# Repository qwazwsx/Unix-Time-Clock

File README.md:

# Introduction

This project is a fork of [Maniacal Labs Super 7 Seg](https://github.com/ManiacalLabs/Super7Seg). Please refer to that project's README for the full details of that project.

My fork was designed with one project in mind - creating a [Unix Time Clock](https://mylifeasa.tinkerer.us/unix-time-clock-57b17d05442e). To accomplish this, I changed the [display hardware](https://github.com/dwaq/Super7Seg/tree/master/kicad/Super7Display) from 6x dual segment displays to 5x displays (12 digits to 10 digits) and changed the [controller hardware](https://github.com/dwaq/Super7Seg/tree/master/kicad/Super7Controller) from a ATMega328p to ESP32. The [Arduino firmware](https://github.com/dwaq/Super7Seg/tree/master/Firmware-ESP32) for this project is also in this repo, along with the [3D models](https://github.com/dwaq/Super7Seg/tree/master/Mount-ESP32) for mounting the project.

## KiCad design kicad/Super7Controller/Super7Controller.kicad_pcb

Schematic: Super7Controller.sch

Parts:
P3: Conn_01x13; Socket_Strip_Straight_1x13_Pitch2.54mm
P4: Conn_01x09; Socket_Strip_Straight_1x09_Pitch2.54mm
R1, R2, R3, R5, R6, R7, R8, R10, R11, R12, R13, R14, R15, R16: 120; R_0805_HandSoldering
U1: ULN2003A; SOIC-16_3.9x9.9mm_Pitch1.27mm
U2: HiLetgo_ESP-WROOM-32_Development_Board; hiletgo_esp-wroom-32_development_board

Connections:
DCD_1: U1.6 (I6), U2.15 (P13)
DCD_2: U1.5 (I5), U2.27 (P16)
DCD_3: U1.4 (I4), U2.26 (P4)
DCD_4: U1.3 (I3), U2.25 (P0)
DCD_5: U1.2 (I2), U2.24 (P2)
DCD_6: U1.1 (I1), U2.23 (P15)
DC_1: P3.1, U1.11 (O6)
DC_2: P3.2, U1.12 (O5)
DC_3: P3.7, U1.13 (O4)
DC_4: P3.8, U1.14 (O3)
DC_5: P3.12, U1.15 (O2)
DC_6: P3.13, U1.16 (O1)
GND: U1.8 (GND), U2.14 (GND)
H_A1: P3.5, R12.2
H_A2: P3.10, R15.2
H_B1: P3.6, R13.2
H_B2: P3.11, R16.2
H_C1: P4.3, R3.2
H_C2: P4.8, R8.2
H_D1: P4.2, R2.2
H_D2: P4.6, R6.2
H_E1: P4.1, R1.2
H_E2: P4.5, R5.2
H_F1: P3.3, R10.2
H_F2: P3.9, R14.2
H_G1: P3.4, R11.2
H_G2: P4.7, R7.2
unnamed: R1.1, U2.13 (P12)
unnamed: R2.1, U2.12 (P14)
unnamed: R3.1, U2.11 (P27)
unnamed: R5.1, U2.9 (P25)
unnamed: R6.1, U2.8 (P33)
unnamed: R7.1, U2.7 (P32)
unnamed: R8.1, U2.10 (P26)
unnamed: R10.1, U2.28 (P17)
unnamed: R11.1, U2.29 (P5)
unnamed: R12.1, U2.30 (P18)
unnamed: R13.1, U2.31 (P19)
unnamed: R14.1, U2.33 (P21)
unnamed: R15.1, U2.36 (P22)
unnamed: R16.1, U2.37, U2.38 (P23)

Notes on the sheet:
Ran out of GPIO outputs to control these pins

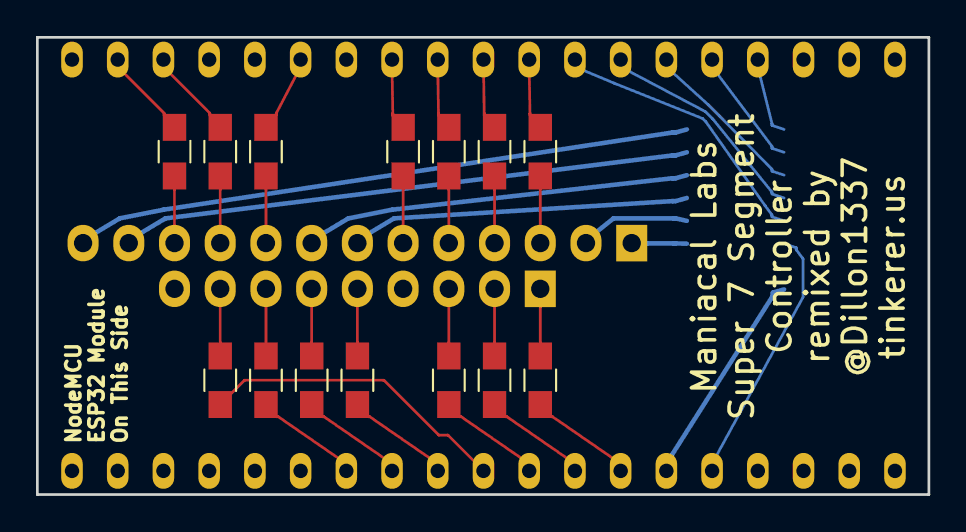
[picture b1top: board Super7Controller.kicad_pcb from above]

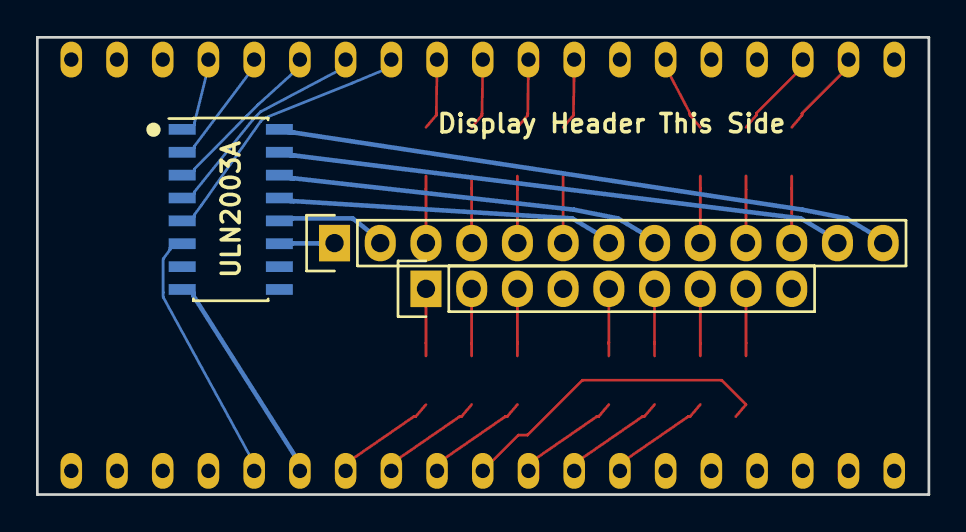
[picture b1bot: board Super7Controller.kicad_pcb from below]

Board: 2 copper layers, 49.5 x 25.4 mm, 18 parts (3 on the bottom side), 41 nets.

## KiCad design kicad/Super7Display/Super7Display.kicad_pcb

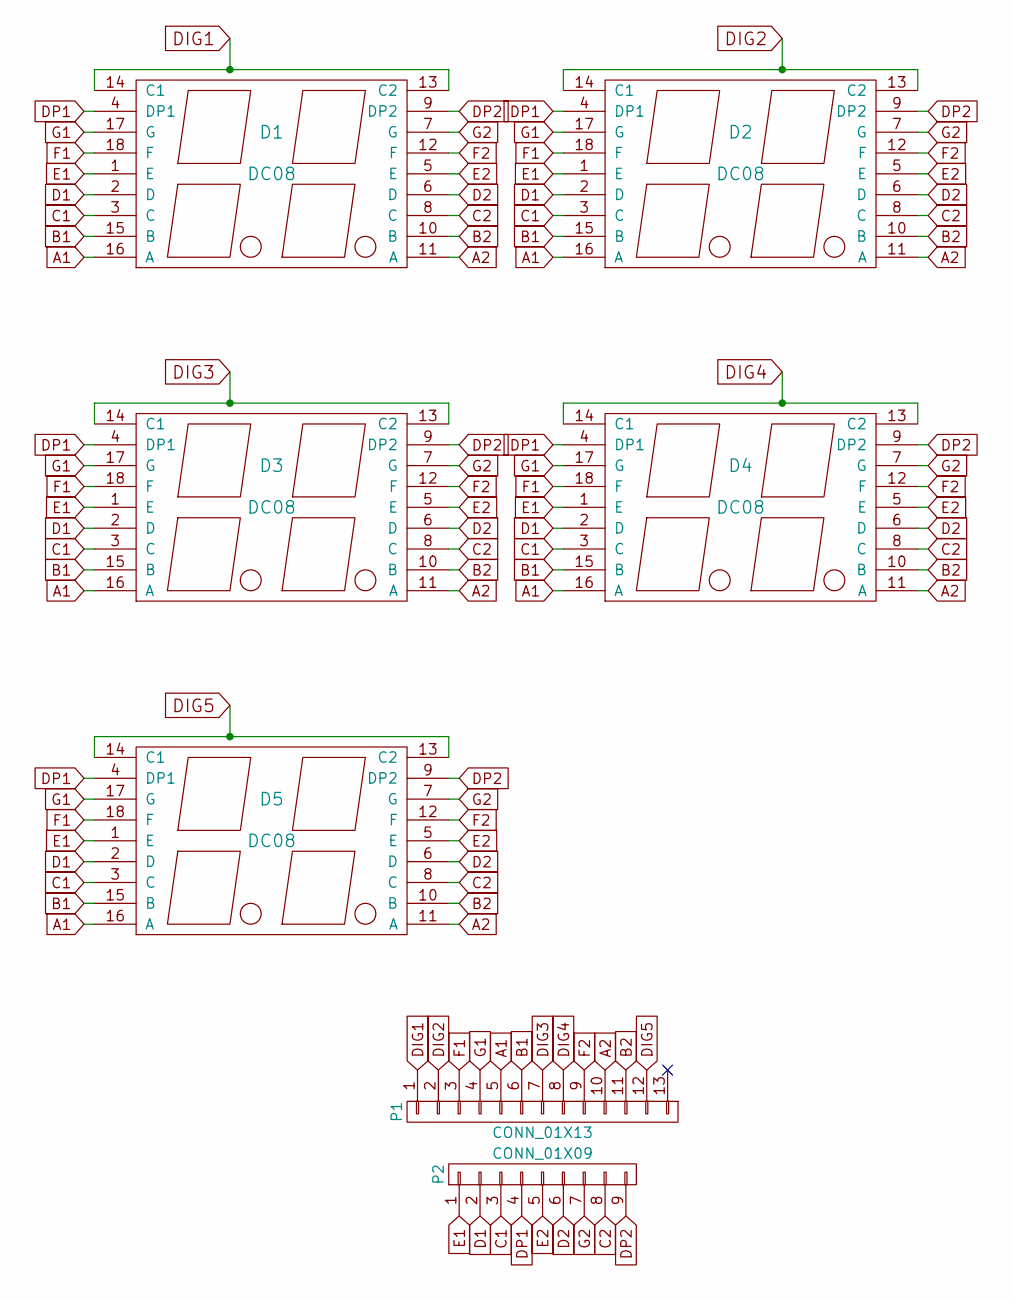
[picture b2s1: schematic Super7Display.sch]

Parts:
D1, D2, D3, D4, D5: DC08
P1: CONN_01X13; Socket_Strip_Straight_1x13
P2: CONN_01X09; Socket_Strip_Straight_1x09

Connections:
A1: D1.16 (A), D2.16 (A), D3.16 (A), D4.16 (A), D5.16 (A), P1.5
A2: D1.11 (A), D2.11 (A), D3.11 (A), D4.11 (A), D5.11 (A), P1.10
B1: D1.15 (B), D2.15 (B), D3.15 (B), D4.15 (B), D5.15 (B), P1.6
B2: D1.10 (B), D2.10 (B), D3.10 (B), D4.10 (B), D5.10 (B), P1.11
C1: D1.3 (C), D2.3 (C), D3.3 (C), D4.3 (C), D5.3 (C), P2.3
C2: D1.8 (C), D2.8 (C), D3.8 (C), D4.8 (C), D5.8 (C), P2.8
D1: D1.2 (D), D2.2 (D), D3.2 (D), D4.2 (D), D5.2 (D), P2.2
D2: D1.6 (D), D2.6 (D), D3.6 (D), D4.6 (D), D5.6 (D), P2.6
DIG1: D1.13 (C2), D1.14 (C1), P1.1
DIG2: D2.13 (C2), D2.14 (C1), P1.2
DIG3: D3.13 (C2), D3.14 (C1), P1.7
DIG4: D4.13 (C2), D4.14 (C1), P1.8
DIG5: D5.13 (C2), D5.14 (C1), P1.12
DP1: D1.4 (DP1), D2.4 (DP1), D3.4 (DP1), D4.4 (DP1), D5.4 (DP1), P2.4
DP2: D1.9 (DP2), D2.9 (DP2), D3.9 (DP2), D4.9 (DP2), D5.9 (DP2), P2.9
E1: D1.1 (E), D2.1 (E), D3.1 (E), D4.1 (E), D5.1 (E), P2.1
E2: D1.5 (E), D2.5 (E), D3.5 (E), D4.5 (E), D5.5 (E), P2.5
F1: D1.18 (F), D2.18 (F), D3.18 (F), D4.18 (F), D5.18 (F), P1.3
F2: D1.12 (F), D2.12 (F), D3.12 (F), D4.12 (F), D5.12 (F), P1.9
G1: D1.17 (G), D2.17 (G), D3.17 (G), D4.17 (G), D5.17 (G), P1.4
G2: D1.7 (G), D2.7 (G), D3.7 (G), D4.7 (G), D5.7 (G), P2.7

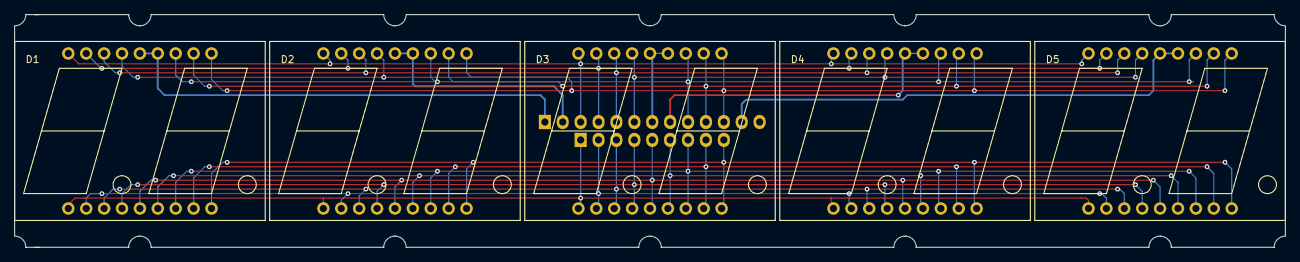
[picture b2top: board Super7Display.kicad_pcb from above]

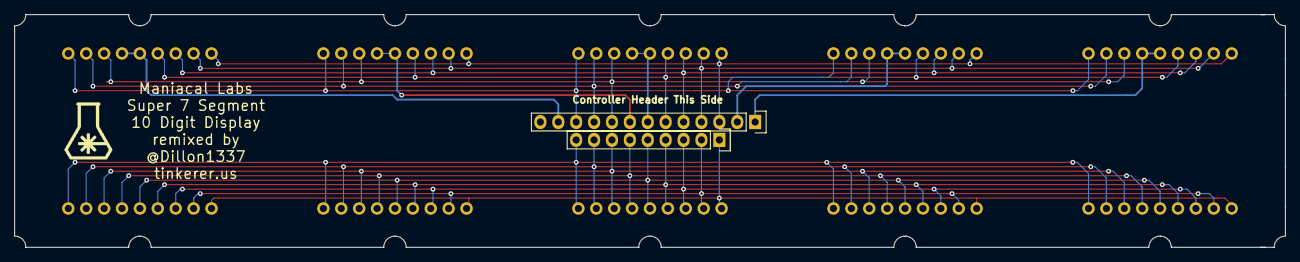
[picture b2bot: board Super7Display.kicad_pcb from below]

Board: 2 copper layers, 180.3 x 33.0 mm, 7 parts (2 on the bottom side), 21 nets.

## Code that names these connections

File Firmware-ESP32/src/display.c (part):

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
// digit is active high
// digit | ESP32 pin
#define DC_1  13
#define DC_2  16
#define DC_3  4
#define DC_4  0
#define DC_5  2
#define DC_6  15

// PWM channels cooresponding to digits
#define D_PWM_1  1
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  //pinMode(SEG_DP2, OUTPUT);

  // set up PWM on digits
  ledcAttachPin(DC_1, D_PWM_1);
  ledcSetup(D_PWM_1, PWM_FREQ, PWM_RESOLUTION);

  ledcAttachPin(DC_2, D_PWM_2);
  ledcSetup(D_PWM_2, PWM_FREQ, PWM_RESOLUTION);

  ledcAttachPin(DC_3, D_PWM_3);
  ledcSetup(D_PWM_3, PWM_FREQ, PWM_RESOLUTION);

  ledcAttachPin(DC_4, D_PWM_4);
  ledcSetup(D_PWM_4, PWM_FREQ, PWM_RESOLUTION);

  ledcAttachPin(DC_5, D_PWM_5);
  ledcSetup(D_PWM_5, PWM_FREQ, PWM_RESOLUTION);

  //ledcAttachPin(DC_6, D_PWM_6);
  //ledcSetup(D_PWM_6, PWM_FREQ, PWM_RESOLUTION);
}

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
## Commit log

2018-01-30 Remove DIG6 from schematic
2018-01-30 regenerate netlist
2018-01-30 Remove D6 from layout
    Move right edge into place
    Top and bottom edges still need adjusted
2018-01-30 Move mounting tabs above/below D1, D3, D5
2018-01-30 use built-in ULN2003
2018-01-30 DC6 is gone
2018-01-30 added no connect on unused segment connector
2018-01-31 add part for ESP32 dev board
2018-01-31 connect ESP dev board on schematic
2018-01-31 change resistors to surface mount
2018-01-31 use old symbol for ULN2003A because GND is needed
2018-01-31 change ESP pins to bidirectional to pass ERC
2018-01-31 use SOIC footprint for ULN
2018-02-07 make new footprint for ESP32
2018-02-07 add to project
2018-02-08 don't need that library here
2018-02-08 ignore some kicad files
2018-02-08 assign pin numers to hiletgo library
2018-02-08 assign esp32 footprint to schematic symbol
2018-02-08 add no connects to unused pins
2018-02-08 generate new netlist
2018-02-08 ignore another type of backup file
2018-02-08 read new netlist and delete all the old stuff
2018-02-08 remove some extra silkscreen
2018-02-08 move around
2018-02-08 move reference inside board
2018-02-08 add anchor
2018-02-08 add anchor to display also
2018-02-08 create TopoR project
2018-02-08 export layout
2018-02-08 import project into TopoR
2018-02-08 export in TopoR format
2018-02-08 these ESP32 GPIOs are swappable
2018-02-08 these ULN outputs are swappable
2018-02-08 autorouted controller
2018-02-08 exported design
2018-02-08 needed to export specctra in Kicad format
2018-02-08 imported routes into kicad
2018-02-08 trying autorouting again - no luck
2018-02-08 these ULN inputs are swappable
2018-02-08 improved routing to ULN
2018-02-08 all resistor inputs are swappable
2018-02-08 make resistor inputs gate swappable
2018-02-08 move ULN to the back
2018-02-08 regenerate files with ULN on the back
2018-02-08 did work
2018-02-08 this one looks pretty good
2018-02-08 move esp on top of headers
2018-02-08 autoroute went ok, want to rotate ESP
2018-02-08 rotated and shifted ESP
2018-02-08 found good routing and placement for components
2018-02-08 import routed design into KiCad
2018-02-08 adjust edge cuts and remove unneeded parts
2018-02-08 only need one ground connection from ESP to ULN
2018-02-08 remove ignored file
2018-02-08 reroute lines to match autorouter
2018-02-08 read new netlist, some errors left
2018-02-08 correct errors in netlist
2018-02-08 replace long ground trace with something shorter
2018-02-08 remove cache
2018-02-08 messed up pinout of ESP schematic symbol
2018-02-08 move resistor connections to make routing easier
2018-02-08 move ULN connections to make routing easier
2018-02-08 export netlist into layout and remove already routed lines
2018-02-08 autorouter worked well on resistors, ULN needs work
2018-02-08 move the ULN up a little
2018-02-08 6 to 2
2018-02-08 2 to 6 is better
2018-02-08 Autoroute it and put it back into KiCad
2018-02-08 remove/hide top layer silkscreen
2018-02-08 move silkscreen away from lines
2018-02-08 new gerbers lookin' good
2018-02-08 use new KiCad header instead of old one
2018-02-08 Add silkscreen for ESP32 pin 1
2018-02-08 add silkscreen to ULN
2018-02-08 latest TopoR files
2018-02-08 new footprint for headers
2018-02-08 latest gerbers
2018-02-08 remove anchor and change silkscreen
2018-02-08 full size gerbers
2018-02-08 Make display's board outline the same size as the digits
    Only saves $5.30 on OSH Park
2018-02-08 change page size and move into center
2018-02-08 change and move text
2018-02-09 regenerate gerbers
2018-02-09 put an edge cut insert in between every digit
2018-02-09 generate new gerbers
2018-02-09 generated gerbers and sent them to OSH Park
2018-02-09 add image of controller schematic
2018-02-28 Installation instructions for new code
2018-02-28 Blinky working for ESP32
2018-02-28 start on display code
    includes some old code from another project
2018-02-28 changed enough that it will compile
2018-02-28 super bare bones main
    but it compiles
2018-02-28 write the rest of the display code
2018-02-28 display an increasing counter
2018-03-02 wrote the pin number instead of GPIO number
2018-03-02 inverted the digit logic
2018-03-02 Use DP1 pin for C2
    GPIOs 34 and 35 are input only (GPI??)
    Not enough pins to control everything
    Since one "bad" pin was already DP2, use DP1's pin to control the other "bad" pin, C2
2018-03-02 count up slower
2018-03-02 new file for wifi credentials
2018-03-02 connect to NTP server and get time and print to display
2018-03-02 remove decimal points from PCB and connect C2 instead
    This shifts the connections on C2, D2, E2, and G2
2018-03-03 break the time into digits in a new function
2018-03-03 only use unix_time in original function
2018-03-03 fix display brightness by delaying between each display
2018-03-03 constantly set time
    doesn't need to be done this way. would be better if it was set every second instead
2018-03-03 comment out Serial functionality
2018-03-03 these lines are needed
2018-03-03 put internet time setting code into its own function
2018-03-05 move getTimeFromInternet() into it's own files
2018-03-05 move time-related functions into getTime
2018-03-05 clean up and add comments to main file
2018-03-05 remove old code
2018-03-05 add comment about delay
2018-03-05 add some comments
2018-03-05 refresh the time every 10000 seconds
2018-03-05 add TODO
2018-03-05 can remove initial getTime
2018-03-06 give me some more time
2018-03-06 automatically get time from internet on startup
2018-03-06 do an animation at startup
2018-03-06 set up some print debugging
2018-03-06 get the time from the internet on the other core
2018-03-06 don't need WiFi time kickstart function anymore
2018-03-06 slow printed data down
2018-03-06 send data through queue to start and stop WiFi connection
2018-03-09 remove constant time print
2018-03-09 remove delay in loop
2018-03-09 display a connecting animation until time is set
2018-03-09 comment out serial prints
2018-03-09 use hardware timer to call setTime() every 1 second
2018-03-10 connect to WiFi at startup and never disconnect
2018-03-10 check time from internet every 10k seconds
2018-03-10 use second core to get time from the internet
2018-03-10 remove all serial.prints
2018-03-10 change comment on digit active high
2018-03-10 add note that 10 is a special number
2018-03-10 clean up comments on Task creator
2018-03-10 add clear definition comment
2018-03-10 never returns, so don't need to delete
2018-03-10 clear up comment on isConnecting function
2018-03-10 comments on unix time
2018-03-10 add note about WiFi settings header
2018-03-10 remove extra spaces
2018-03-10 adjust digital digit drivers with PWM drivers
2018-03-10 (BUG FIX): DC_6 is on P15, PIN 23
2018-03-10 remove old digit digital drive code
2018-03-10 replace hardcoded PWM channels with #defines
2018-03-10 use PWM_BRIGHTNESS on all digits and explain how to change it
2018-04-02 3D printed bracket for mounting the ESP32 controller and 10 digit display
    File is heavily modified since I last printed it. My 3D print required a lot of changes with a sharp blade. I tried to miror those changes in this file but I haven't printed this design to know if it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
2018-04-02 restart ESP32 if it doesn't connect to WiFi at startup
2018-04-02 move hardware timer code into new function
2018-04-02 fix up comment
2018-04-02 set up hardware timer aligned with actual time
    performed automatically at startup
2018-05-03 Apply bodge wire fix to controller PCB
    Decimal points are no longer connected
2018-05-03 regenerate controller gerbers
2018-05-03 export image of modified schematic
2018-05-03 export image of display schematic
2018-05-04 ignore visual micro generated files
2018-08-08 initialize platformio inside visual studio code
2018-08-08 move all source code into src directory
2018-08-08 implicitly add Time library for time()
2018-08-08 add default case for getDigit()
    It displays the refresh line "--", which is bad behavior, but hopefully this case will never happen
2018-08-08 spell check to the rescue
2019-04-25 time() returns a 32 bit value
2019-04-25 ignore vscode configs
2019-04-25 example of the accurate unix time printed using python
2019-04-25 actually ignore vscode configs
2019-04-25 constantly get the time and then display it
    instead of only getting the time every second from the hardware timer
2019-04-26 Spread out the digit calculation over the displays & refresh time every hour
    Last commit heavily front-loaded the time calculation. It got the time and determined every digit to display AND THEN displayed each of those digits. Now it gets the time and the two digits for one d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
    This also reuses the hardware timer to re-sync the time from the internet every hour. All it does is set a flag so the other core will get the time so this also shouldn't affect the display.
2019-05-16 don't need to wait for second to change to display an accurate value
2019-05-16 use the hardware timer to update the time from the internet every hour
2019-05-16 Update README for my project details
2019-05-16 remove all unused files from original project
2019-05-16 Add image of project to README
2019-05-23 Change divider on HW timer from 1us to 100us
    This should help to prevent the timerAlarmWrite issue. interruptAt is now 26 bits instead of 32 bits
2019-12-02 math makes it easier to set digits from right to left
    under the assumption before that digits were set left to right which caused the display to be mirrored
2019-12-02 wait for second to change to display an accurate value
2019-12-20 return a 64 bit value from getTime()
2022-05-19 added delay to selectDisplay() to prevent ghosting
